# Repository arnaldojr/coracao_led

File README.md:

coracao_led
===========

desenvolvimento de um placa no formato de um coração rodeado de Led.

Microcontrolado por um pic18f452;
Acelerometro adxl345 para detecção de movimentos;
Conversor DC/DC step-Up 3v/5v para alimentação por pilha;
Saida serial para PC;

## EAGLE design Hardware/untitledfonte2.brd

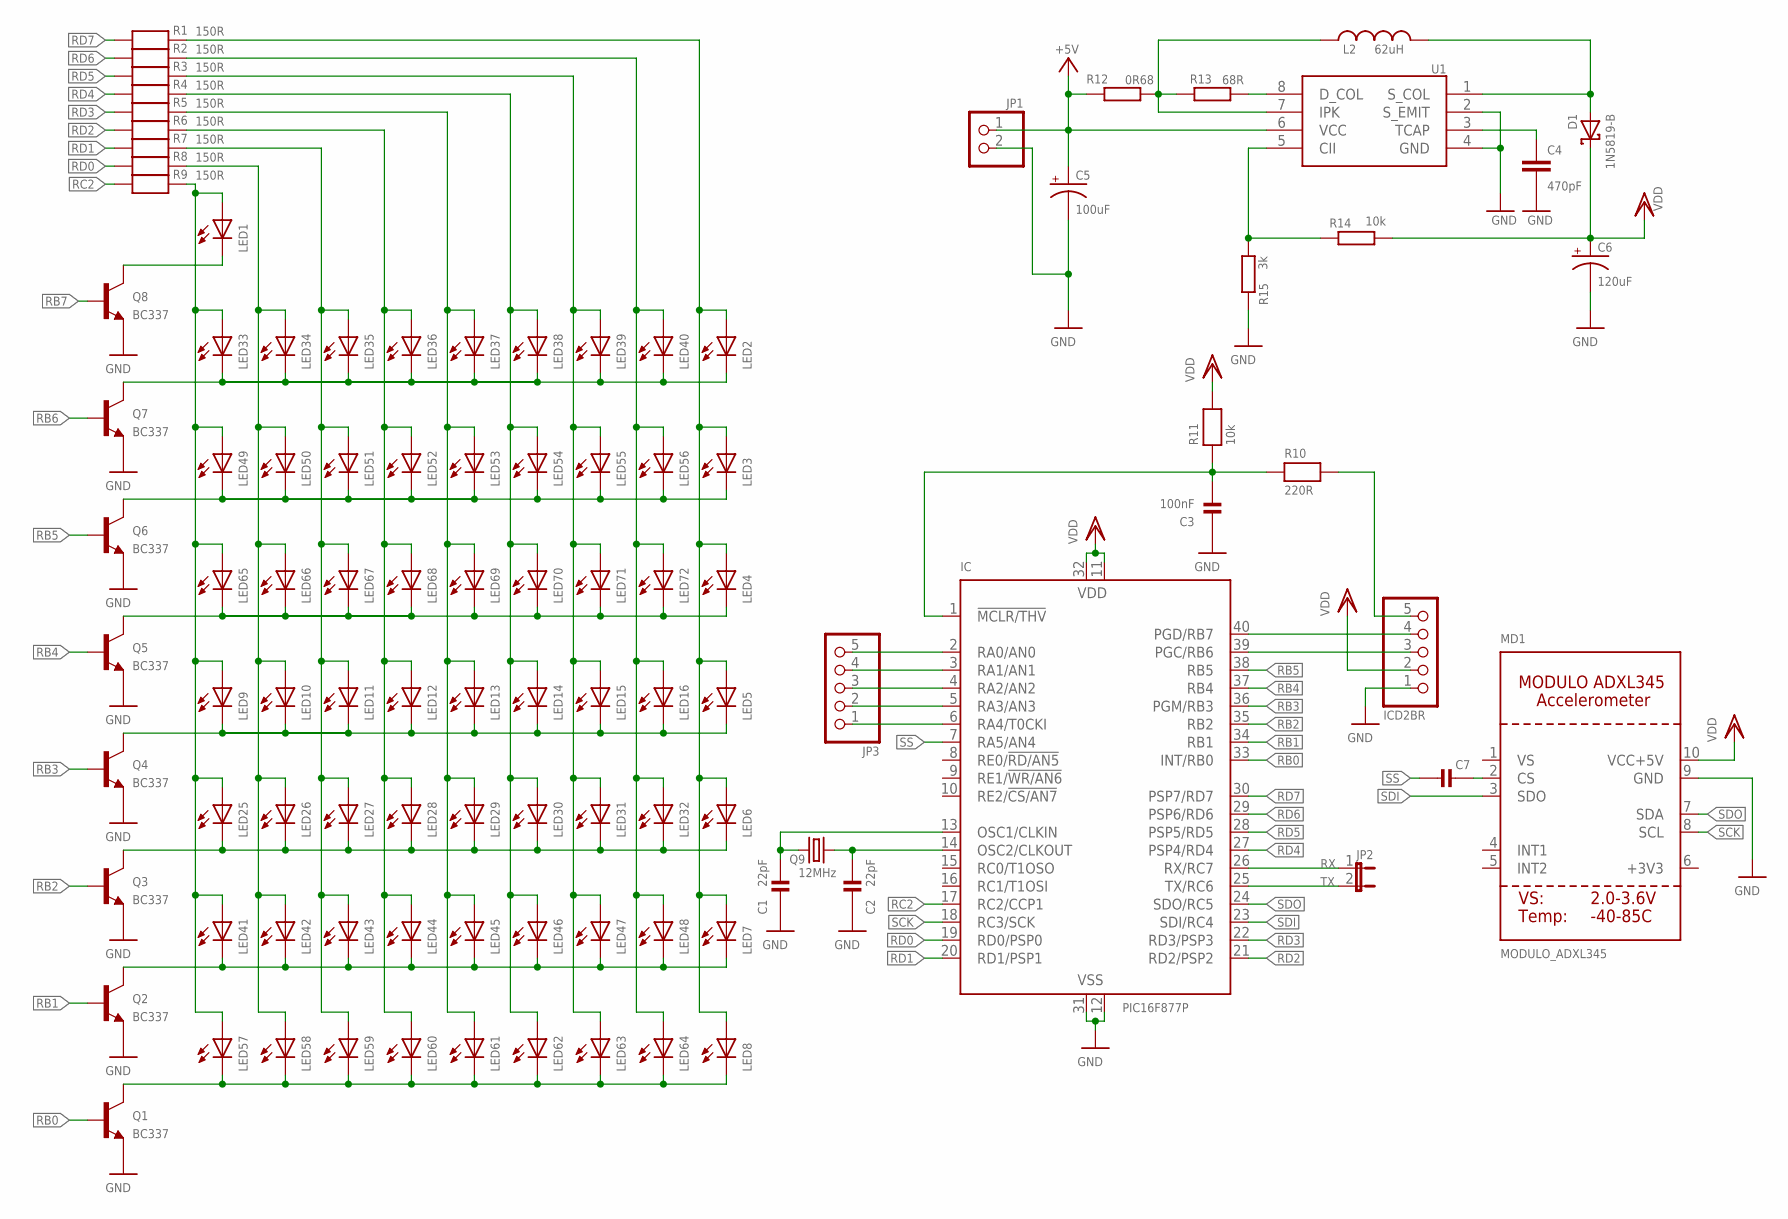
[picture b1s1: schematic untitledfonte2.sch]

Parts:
C1, C2: 22pF; 0805_NOTHERMALS
C3: 100nF; 0805_NOTHERMALS
C4: 470pF; C0805
C5: 100uF; E2,5-5
C6: 120uF; E2,5-5
C7: CAP_CERAMIC0805-NOTHERMALS; 0805_NOTHERMALS
D1: 1N5819-B; DO41-7.6
IC: PIC16F877P; DIL40
ICD2BR: HEADER-1X5ROUND; 1X05_ROUND
JP1: HEADER-1X2; 1X02_OVAL
JP2: JUMPER2
JP3: HEADER-1X5ROUND; 1X05_ROUND
L2: 62uH; 0204/5
LED1, LED2, LED3, LED4, LED5, LED6, LED7, LED8, LED9, LED10, LED11, LED12, LED13, LED14, LED15, LED16, LED25, LED26, LED27, LED28, LED29, LED30, LED31, LED32, LED33, LED34, LED35, LED36, LED37, LED38, LED39, LED40, LED41, LED42, LED43, LED44, LED45, LED46, LED47, LED48, LED49, LED50, LED51, LED52, LED53, LED54, LED55, LED56, LED57, LED58, LED59, LED60, LED61, LED62, LED63, LED64, LED65, LED66, LED67, LED68, LED69, LED70, LED71, LED72: LED3MM
MD1: MODULO_ADXL345
Q1, Q2, Q3, Q4, Q5, Q6, Q7, Q8: BC337; TO92
Q9: 12MHz; HC49/S
R1, R2, R3, R4, R5, R6, R7, R8, R9: 150R; 0805_NOTHERMALS
R10: 220R; 0805_NOTHERMALS
R11: 10k; 0805_NOTHERMALS
R12: 0R68; 0207/5V
R13: 68R; 0207/2V
R14: 10k; 0207/2V
R15: 3k; 0207/2V
U1: MC34063A; SOIC8_150MIL

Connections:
1: D1.A, L2.2, U1.1 (S_COL)
3: C4.1, U1.3 (TCAP)
5: R14.1, R15.2, U1.5 (CII)
7: L2.1, R12.2, R13.1, U1.7 (IPK)
8: R13.2, U1.8 (D_COL)
+5V: C5.+, JP1.1, R12.1, U1.6 (VCC)
GND: C1.1, C2.1, C3.1, C4.2, C5.-, C6.-, IC.12 (VSS), IC.31 (VSS), ICD2BR.1, JP1.2, MD1.9 (GND), Q1.1 (E), Q2.1 (E), Q3.1 (E), Q4.1 (E), Q5.1 (E), Q6.1 (E), Q7.1 (E), Q8.1 (E), R15.1, U1.2 (S_EMIT), U1.4 (GND)
unnamed: LED1.K (C), Q8.3 (C)
unnamed: C7.1, MD1.2 (CS)
unnamed: LED4.K (C), LED65.K (C), LED66.K (C), LED67.K (C), LED68.K (C), LED69.K (C), LED70.K (C), LED71.K (C), LED72.K (C), Q5.3 (C)
unnamed: LED3.K (C), LED49.K (C), LED50.K (C), LED51.K (C), LED52.K (C), LED53.K (C), LED54.K (C), LED55.K (C), LED56.K (C), Q6.3 (C)
unnamed: LED8.K (C), LED57.K (C), LED58.K (C), LED59.K (C), LED60.K (C), LED61.K (C), LED62.K (C), LED63.K (C), LED64.K (C), Q1.3 (C)
unnamed: LED7.K (C), LED41.K (C), LED42.K (C), LED43.K (C), LED44.K (C), LED45.K (C), LED46.K (C), LED47.K (C), LED48.K (C), Q2.3 (C)
unnamed: LED1.A, LED9.A, LED25.A, LED33.A, LED41.A, LED49.A, LED57.A, LED65.A, R9.2
unnamed: LED10.A, LED26.A, LED34.A, LED42.A, LED50.A, LED58.A, LED66.A, R8.2
unnamed: LED11.A, LED27.A, LED35.A, LED43.A, LED51.A, LED59.A, LED67.A, R7.2
unnamed: LED12.A, LED28.A, LED36.A, LED44.A, LED52.A, LED60.A, LED68.A, R6.2
unnamed: LED2.K (C), LED33.K (C), LED34.K (C), LED35.K (C), LED36.K (C), LED37.K (C), LED38.K (C), LED39.K (C), LED40.K (C), Q7.3 (C)
unnamed: LED13.A, LED29.A, LED37.A, LED45.A, LED53.A, LED61.A, LED69.A, R5.2
unnamed: LED14.A, LED30.A, LED38.A, LED46.A, LED54.A, LED62.A, LED70.A, R4.2
unnamed: LED5.K (C), LED9.K (C), LED10.K (C), LED11.K (C), LED12.K (C), LED13.K (C), LED14.K (C), LED15.K (C), LED16.K (C), Q4.3 (C)
unnamed: LED15.A, LED31.A, LED39.A, LED47.A, LED55.A, LED63.A, LED71.A, R3.2
unnamed: LED16.A, LED32.A, LED40.A, LED48.A, LED56.A, LED64.A, LED72.A, R2.2
unnamed: LED2.A, LED3.A, LED4.A, LED5.A, LED6.A, LED7.A, LED8.A, R1.2
unnamed: IC.2 (RA0/AN0), JP3.5
unnamed: IC.3 (RA1/AN1), JP3.4
unnamed: IC.4 (RA2/AN2), JP3.3
unnamed: IC.5 (RA3/AN3), JP3.2
unnamed: IC.6 (RA4/T0CKI), JP3.1
unnamed: LED6.K (C), LED25.K (C), LED26.K (C), LED27.K (C), LED28.K (C), LED29.K (C), LED30.K (C), LED31.K (C), LED32.K (C), Q3.3 (C)
unnamed: C1.2, IC.13 (OSC1/CLKIN), Q9.2
unnamed: C2.2, IC.14 (OSC2/CLKOUT), Q9.1
unnamed: ICD2BR.5, R10.2
unnamed: C3.2, IC.1 (!MCLR/THV), R10.1, R11.1
RB0: IC.33 (INT/RB0), Q1.2 (B)
RB1: IC.34 (RB1), Q2.2 (B)
RB2: IC.35 (RB2), Q3.2 (B)
RB3: IC.36 (PGM/RB3), Q4.2 (B)
RB4: IC.37 (RB4), Q5.2 (B)
RB5: IC.38 (RB5), Q6.2 (B)
RB6: IC.39 (PGC/RB6), ICD2BR.3, Q7.2 (B)
RB7: IC.40 (PGD/RB7), ICD2BR.4, Q8.2 (B)
RC2: IC.17 (RC2/CCP1), R9.1
RD0: IC.19 (RD0/PSP0), R8.1
RD1: IC.20 (RD1/PSP1), R7.1
RD2: IC.21 (RD2/PSP2), R6.1
RD3: IC.22 (RD3/PSP3), R5.1
RD4: IC.27 (PSP4/RD4), R4.1
RD5: IC.28 (PSP5/RD5), R3.1
RD6: IC.29 (PSP6/RD6), R2.1
RD7: IC.30 (PSP7/RD7), R1.1
RX: IC.26 (RX/RC7), JP2.1
SCK: IC.18 (RC3/SCK), MD1.8 (SCL)
SDI: IC.23 (SDI/RC4), MD1.3 (SDO)
SDO: IC.24 (SDO/RC5), MD1.7 (SDA)
SS: C7.2, IC.7 (RA5/AN4)
TX: IC.25 (TX/RC6), JP2.2
VDD: C6.+, D1.C, IC.11 (VDD), IC.32 (VDD), ICD2BR.2, MD1.10 (VCC+5V), R11.2, R14.2

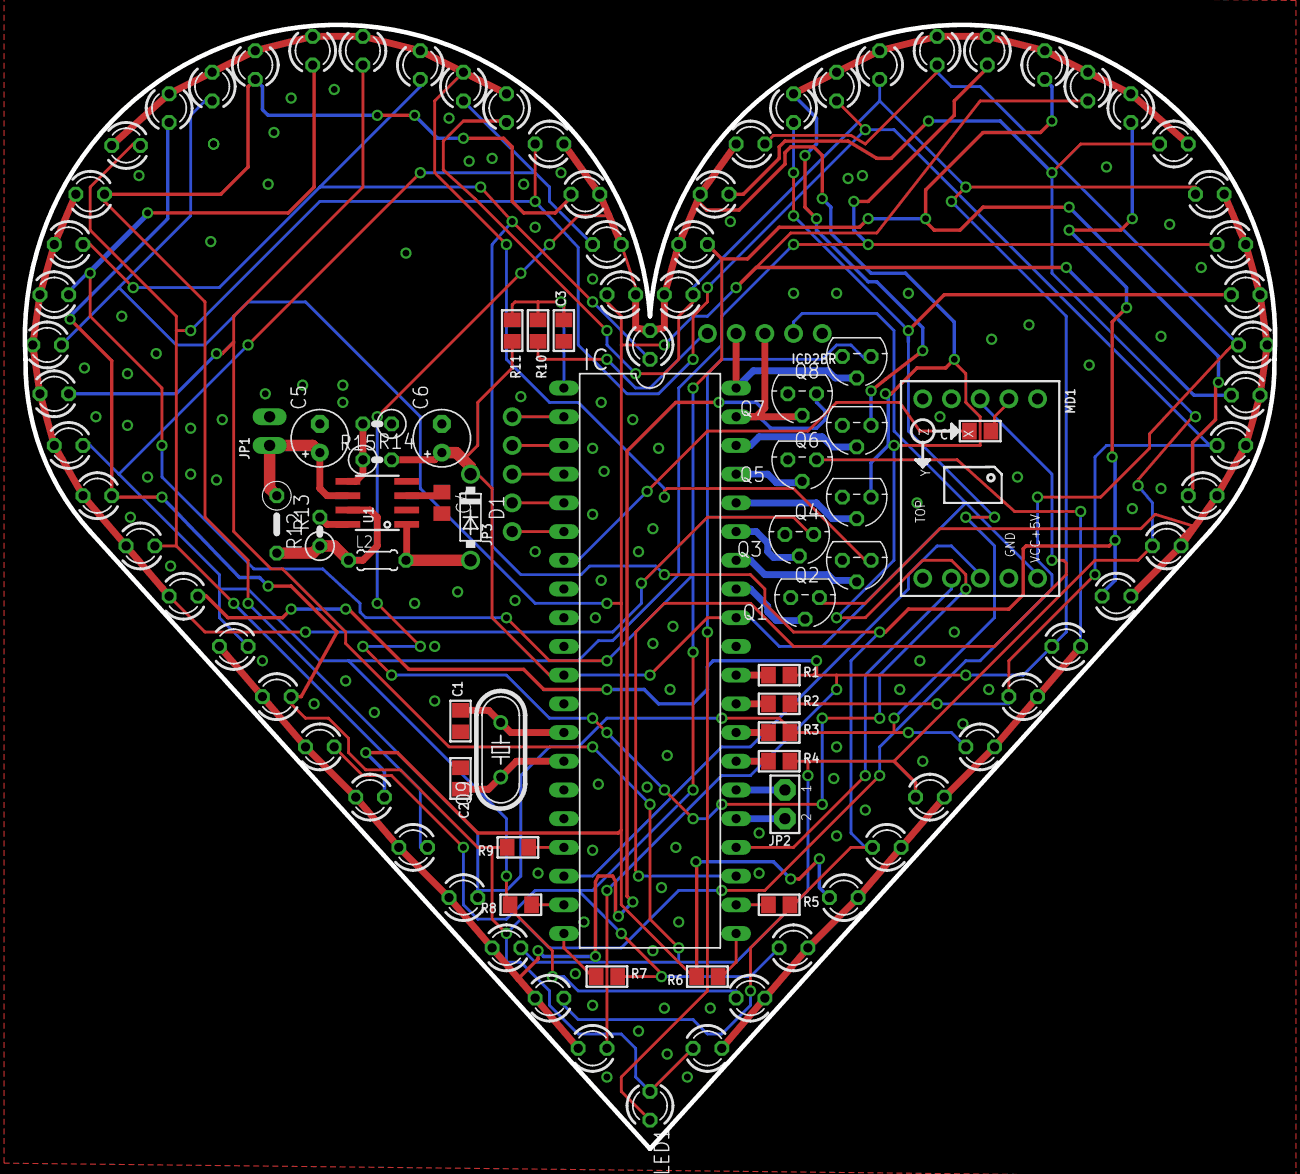
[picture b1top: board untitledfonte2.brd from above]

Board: 2 copper layers, 110.6 x 99.4 mm, 104 parts (0 on the bottom side), 58 nets.

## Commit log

2014-07-24 projeto
    primeira versão
2014-07-24 Placa PCI
    Projeto desenvolvido no Eagle 6.2.
2014-07-24 atualização das pastas
    criada pasta sofware
2014-07-24 atualização da pasta
2014-07-24 Outros
    lista de materiais, imagens.
2014-07-24 Create teste
2014-07-26 mapeamento dos leds
    todos os led estão mapeados no sentido anti-horario
2014-07-27 acende um por vez
    acende todos leds no sentido anti-horario, depois no sentido horario.
2014-07-30 Pisca pisca
    com problema na placa led5,led12, led13
2014-07-30 PISCA PISCA
    mapeado todos os leds para acender na seguencia um por vez no sentido
    horario..

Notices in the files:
parts and their libraries:
microbuilder: This work is placed in the public domain, and may be freely used for commercial and non-commercial work with the following conditions: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
